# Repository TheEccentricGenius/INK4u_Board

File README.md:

# INK4u_Board

An UNO form factor board with a AVR128DA28 processor.

This board is designed to be the next generation AVR succesor to the UNO R3 using the AVR128DA28 from Microchip.

The board has a number of features, such as a UPDI programming and UART programming onboard.
The on-board UPDI programming means a bootloader can be burned onto the MCU while it is on the board....No more external programmer required for programming via the ISP header!

## Pinout for your INK 4u board.

## How to select a upload mode on your INK 4u board.
<i>Credits for the upload mode design goes to MCUdude.</i>

Locate the upload mode header using the pinout as a guide.
Below the upload mode header will be the words "UART AUTO UPDI", when shipped the AUTO mode is selected.

To select UART mode, move the jumper shunt to above the UART word.
</br>

To select UPDI mode, move the jumper shunt to above the UPDI word.
</br>

Return the jumper shunt to AUTO mode if you desire the board to automatically select UART or UPDI.
</br>

## Using the INK 4u board as a UPDI programmer.
1. Select UPDI mode on the upload mode header using the upload mode jumper.
2. Remove the jumper from the UPDI header.
3. Connect the UPDI chip you desire to program or debug via UPDI, to the UPDI pin on the INK 4u board.
   <br><i>Refer to the UPDI mode picture for the UPDI output pin.</i></br>
5. Wire your chip to the respective Power pin from the INK 4u board and the GND pins.
   <br><i>Refer to the pinout for power and GND pins.</i></br>
7. Connect the INK 4u board to your device via the USB B port.
8. Select the INK 4u COM port as your programmer and program using UPDI as normal.

## Configuring your INK 4u board to run in 3.3V mode.
1. Disconnect your board from any power source.
2. Cut the 5V trace as indicated in the photo below.
   </br>

<br><i>Before soldering across the two pads in the blue box, measure the IOREF pin voltage.</i></br>
4. If the IOREF voltage is less then 5V then, solder across the two pads outlined by the blue box.
5. Reconnect the board to a power source, the IOREF voltage should measure close to 3.3V.
   <br><i>If the IOREF voltage is 5V or considerably less then 3.3V repeat the above steps.</i></br>
6. To return the board back to 5V solder across to the pad with the arrow underneath it, and remove the solder connecting to the 3.3V pad.

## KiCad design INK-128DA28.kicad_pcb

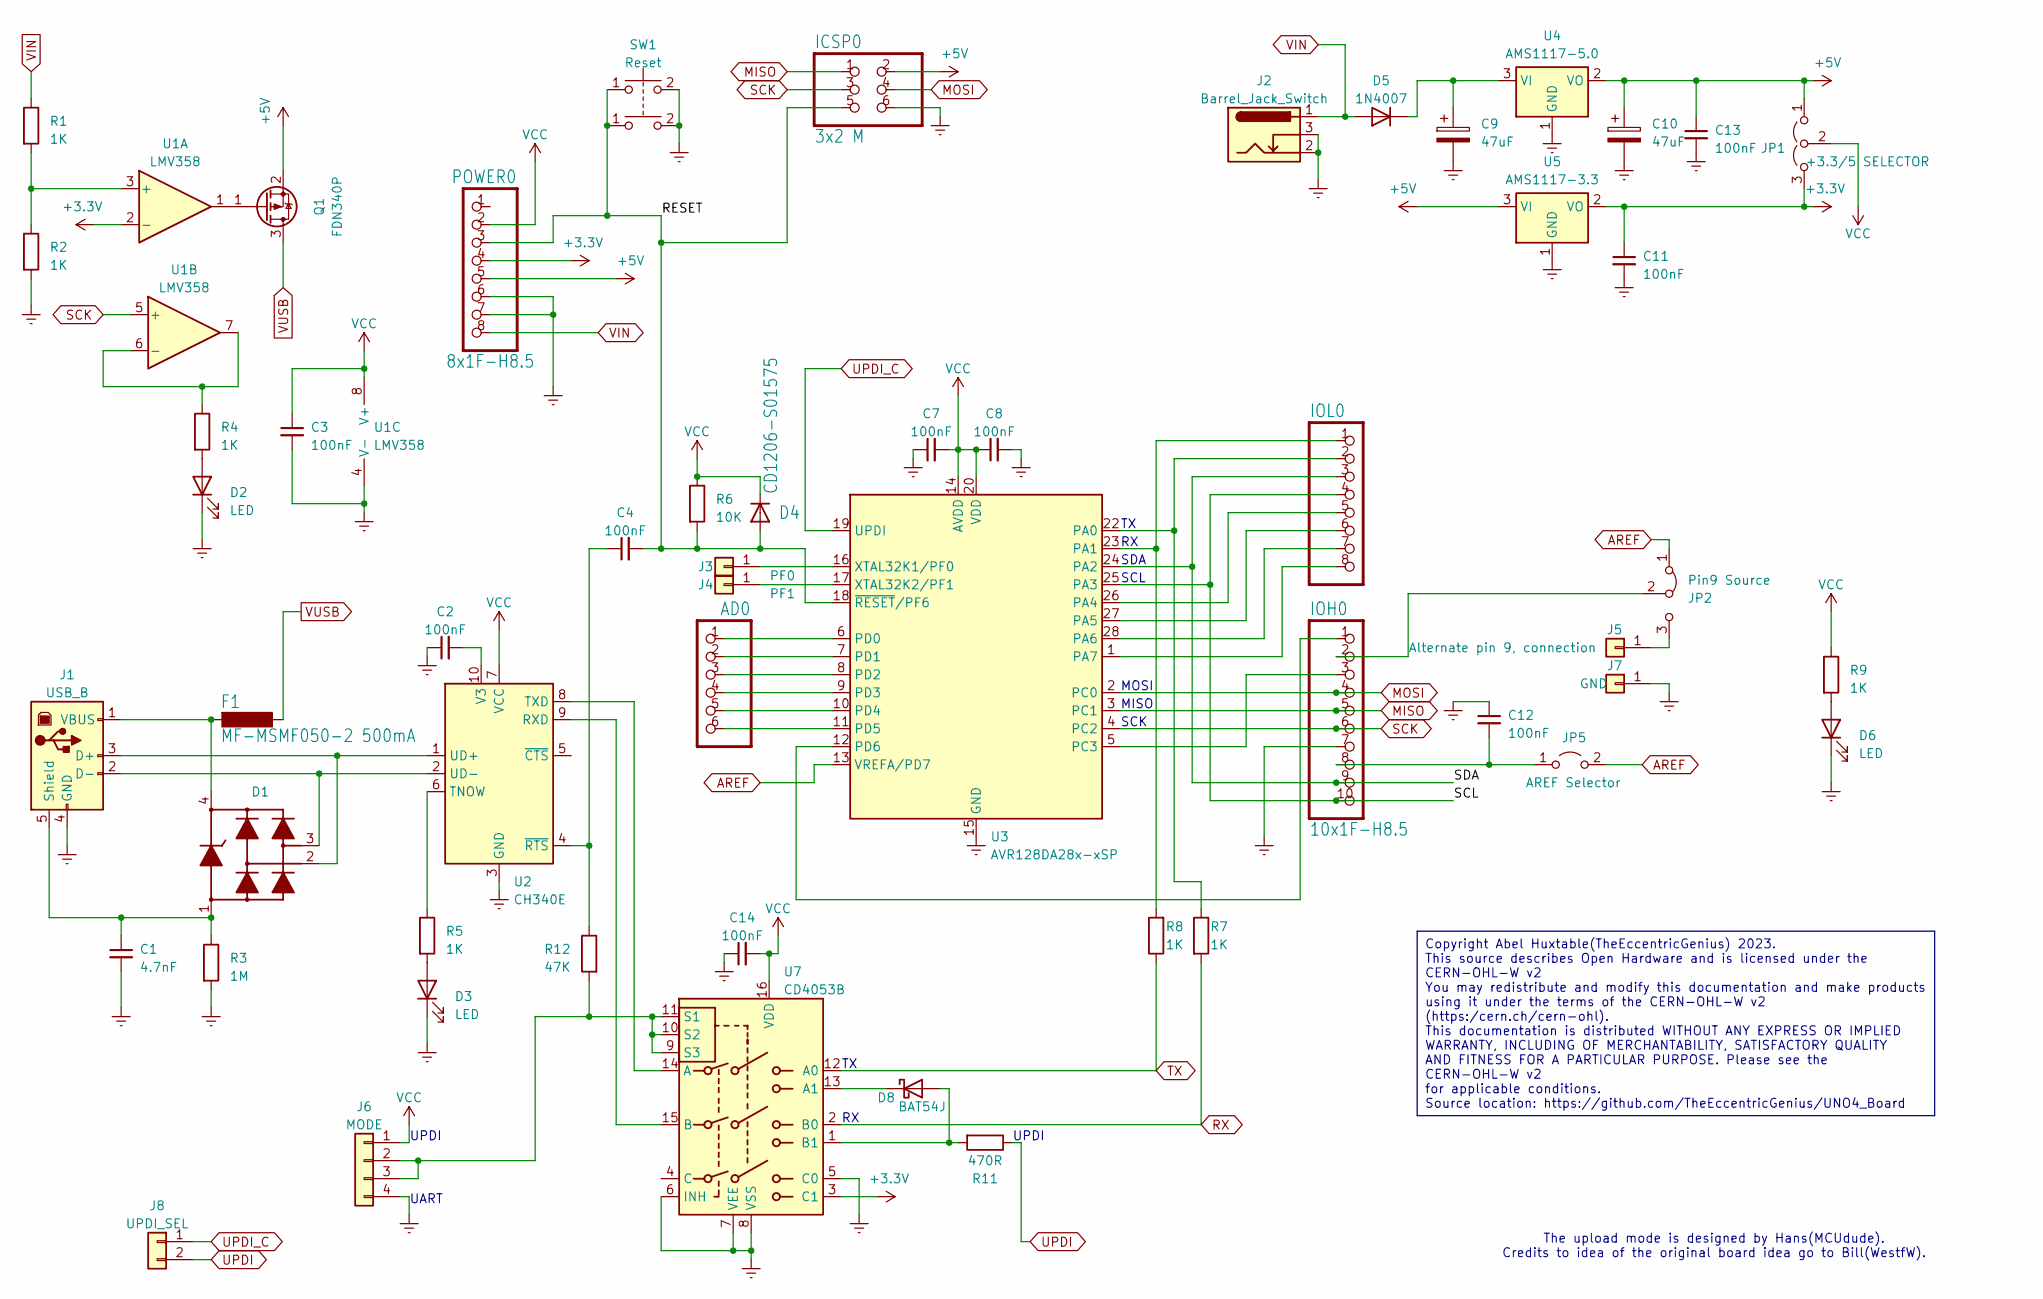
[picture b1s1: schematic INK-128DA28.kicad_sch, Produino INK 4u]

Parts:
AD0: 6x1F-H8.5; PinSocket_1x06_P2.54mm_Vertical
C1: 4.7nF; C_0805_2012Metric_Pad1.18x1.45mm_HandSolder
C2, C3, C4, C7, C8, C11, C12, C13, C14: 100nF; C_0603_1608Metric_Pad1.08x0.95mm_HandSolder
C9, C10: 47uF; CP_Radial_D5.0mm_P2.50mm
D1: PRTR5V0U2X,215; SOT-143_Handsoldering; PART NUMBER PRTR5V0U2X,215
D2, D3, D6: LED; LED_0805_2012Metric_Pad1.15x1.40mm_HandSolder
D4: CD1206-S01575; MINIMELF
D5: 1N4007; D_DO-41_SOD81_P10.16mm_Horizontal
D8: BAT54J; D_SOD-323F
F1: MF-MSMF050-2 500mA; Fuse_1812_4532Metric_Pad1.30x3.40mm_HandSolder
ICSP0: 3x2 M; PinHeader_2x03_P2.54mm_Vertical
IOH0: 10x1F-H8.5; PinSocket_1x10_P2.54mm_Vertical
IOL0: 8x1F-H8.5; PinSocket_1x08_P2.54mm_Vertical
J1: USB_B
J2: Barrel_Jack_Switch; BarrelJack
J3: PF0; SolderWirePad_1x01_SMD_1x2mm
J4: PF1; SolderWirePad_1x01_SMD_1x2mm
J5: Alternate pin 9, connection; SolderWirePad_1x01_SMD_1x2mm
J6: MODE; PinHeader_1x04_P2.54mm_Vertical
J7: GND; SolderWirePad_1x01_SMD_1x2mm
J8: UPDI_SEL; PinHeader_1x02_P2.54mm_Vertical
JP1: +3.3/5 SELECTOR; SolderJumper-3_P1.3mm_Bridged12_RoundedPad1.0x1.5mm
JP2: Pin9 Source; SolderJumper-3_P1.3mm_Bridged12_RoundedPad1.0x1.5mm
JP5: AREF Selector; SolderJumper-2_P1.3mm_Open_RoundedPad1.0x1.5mm
POWER0: 8x1F-H8.5; PinSocket_1x08_P2.54mm_Vertical
Q1: FDN340P; SOT-23
R1, R2, R4, R5, R7, R8, R9: 1K; R_0603_1608Metric_Pad0.98x0.95mm_HandSolder
R3: 1M; R_0603_1608Metric_Pad0.98x0.95mm_HandSolder
R6: 10K; R_0603_1608Metric_Pad0.98x0.95mm_HandSolder
R11: 470R; R_0603_1608Metric_Pad0.98x0.95mm_HandSolder
R12: 47K; R_0603_1608Metric_Pad0.98x0.95mm_HandSolder
SW1: Reset; SW_PUSH_6mm
U1: LMV358; SO-8_3.9x4.9mm_P1.27mm
U2: CH340E; MSOP-10_3x3mm_P0.5mm
U3: AVR128DA28x-xSP; DIP-28_W7.62mm
U4: AMS1117-5.0; SOT-223-3_TabPin2
U5: AMS1117-3.3; SOT-223-3_TabPin2
U7: CD4053B; TSSOP-16_4.4x5mm_P0.65mm

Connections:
+3.3V: C11.1, JP1.3 (B), POWER0.4, U1.2 (-), U5.2 (VO), U7.3 (C1)
+5V: C10.1, C13.1, ICSP0.2, JP1.1 (A), POWER0.5, Q1.2 (S), U4.2 (VO), U5.3 (VI)
/RESET: C4.2, D4.A, ICSP0.5, POWER0.3, R6.2, SW1.1 (3), U3.18 (~RESET/PF6)
/SCL: IOH0.10, IOL0.4, U3.25 (PA3)
/SDA: IOH0.9, IOL0.3, U3.24 (PA2)
AREF: JP2.1 (A), JP5.2 (B), U3.13 (VREFA/PD7)
Earth: C1.2, C2.1, C3.2, C7.1, C8.2, C9.2, C10.2, C11.2, C12.1, C13.2, C14.1, D2.1 (K), D3.1 (K), D6.1 (K), ICSP0.6, IOH0.7, J1.4 (GND), J2.2, J2.3, J6.4, J7.1, POWER0.6, POWER0.7, R2.2, R3.2, SW1.2 (4), U1.4 (V-), U2.3 (GND), U3.15 (GND), U3.21 (GND), U4.1 (GND), U5.1 (GND), U7.5 (C0), U7.6 (INH), U7.7 (VEE), U7.8 (VSS)
MISO: ICSP0.1, IOH0.5, U3.3 (PC1)
MOSI: ICSP0.4, IOH0.4, U3.2 (PC0)
unnamed: D2.2 (A), R4.2
unnamed: D3.2 (A), R5.2
unnamed: C9.1, D5.1 (K), U4.3 (VI)
unnamed: D6.2 (A), R9.2
unnamed: D8.2 (A), R11.2, U7.1 (B1)
unnamed: D8.1 (K), U7.13 (A1)
unnamed: D1.2, J1.3 (D+), U2.1 (UD+)
unnamed: D1.3, J1.2 (D-), U2.2 (UD-)
unnamed: C1.1, D1.1, J1.5 (Shield), R3.1
unnamed: D1.4, F1.2, J1.1 (VBUS)
unnamed: J3.1, U3.16 (XTAL32K1/PF0)
unnamed: J4.1, U3.17 (XTAL32K2/PF1)
unnamed: J5.1, JP2.3 (B)
unnamed: J6.2, J6.3, R12.2, U7.9 (S3), U7.10 (S2), U7.11 (S1)
unnamed: IOH0.2, JP2.2 (C)
unnamed: C12.2, IOH0.8, JP5.1 (A)
unnamed: Q1.1 (G), U1.1
unnamed: R1.2, R2.1, U1.3 (+)
unnamed: R4.1, U1.6 (-), U1.7
unnamed: U2.9 (RXD), U7.15 (B)
unnamed: R5.1, U2.6 (TNOW)
unnamed: U2.8 (TXD), U7.14 (A)
unnamed: C2.2, U2.10 (V3)
unnamed: C4.1, R12.1, U2.4 (~RTS)
unnamed: IOL0.2, R7.1, U3.22 (PA0)
unnamed: IOL0.1, R8.2, U3.23 (PA1)
unnamed: IOL0.5, U3.26 (PA4)
unnamed: IOL0.6, U3.27 (PA5)
unnamed: IOL0.7, U3.28 (PA6)
unnamed: IOL0.8, U3.1 (PA7)
unnamed: IOH0.3, U3.5 (PC3)
unnamed: AD0.1, U3.6 (PD0)
unnamed: AD0.2, U3.7 (PD1)
unnamed: AD0.3, U3.8 (PD2)
unnamed: AD0.4, U3.9 (PD3)
unnamed: AD0.5, U3.10 (PD4)
unnamed: AD0.6, U3.11 (PD5)
unnamed: IOH0.1, U3.12 (PD6)
RX: R7.2, U7.2 (B0)
SCK: ICSP0.3, IOH0.6, U1.5 (+), U3.4 (PC2)
TX: R8.1, U7.12 (A0)
UPDI: J8.2, R11.1
UPDI_C: J8.1, U3.19 (UPDI)
VCC: C3.1, C7.2, C8.1, C14.2, D4.C, J6.1, JP1.2 (C), POWER0.2, R6.1, R9.1, U1.8 (V+), U2.7 (VCC), U3.14 (AVDD), U3.20 (VDD), U7.16 (VDD)
VIN: D5.2 (A), J2.1, POWER0.8, R1.1
VUSB: F1.1, Q1.3 (D)

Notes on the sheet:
Copyright Abel Huxtable(TheEccentricGenius) 2023. This source describes Open Hardware and is licensed under the CERN-OHL-W v2 You may redistribute and modify this documentation and make products using it under the terms of the CERN-OHL-W v2 (https:/cern.ch/cern-ohl). This documentation is distribut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
UART
SCK
SDA
MISO
SCL
UPDI
MOSI
The upload mode is designed by Hans(MCUdude). Credits to idea of the original board idea go to Bill(WestfW).

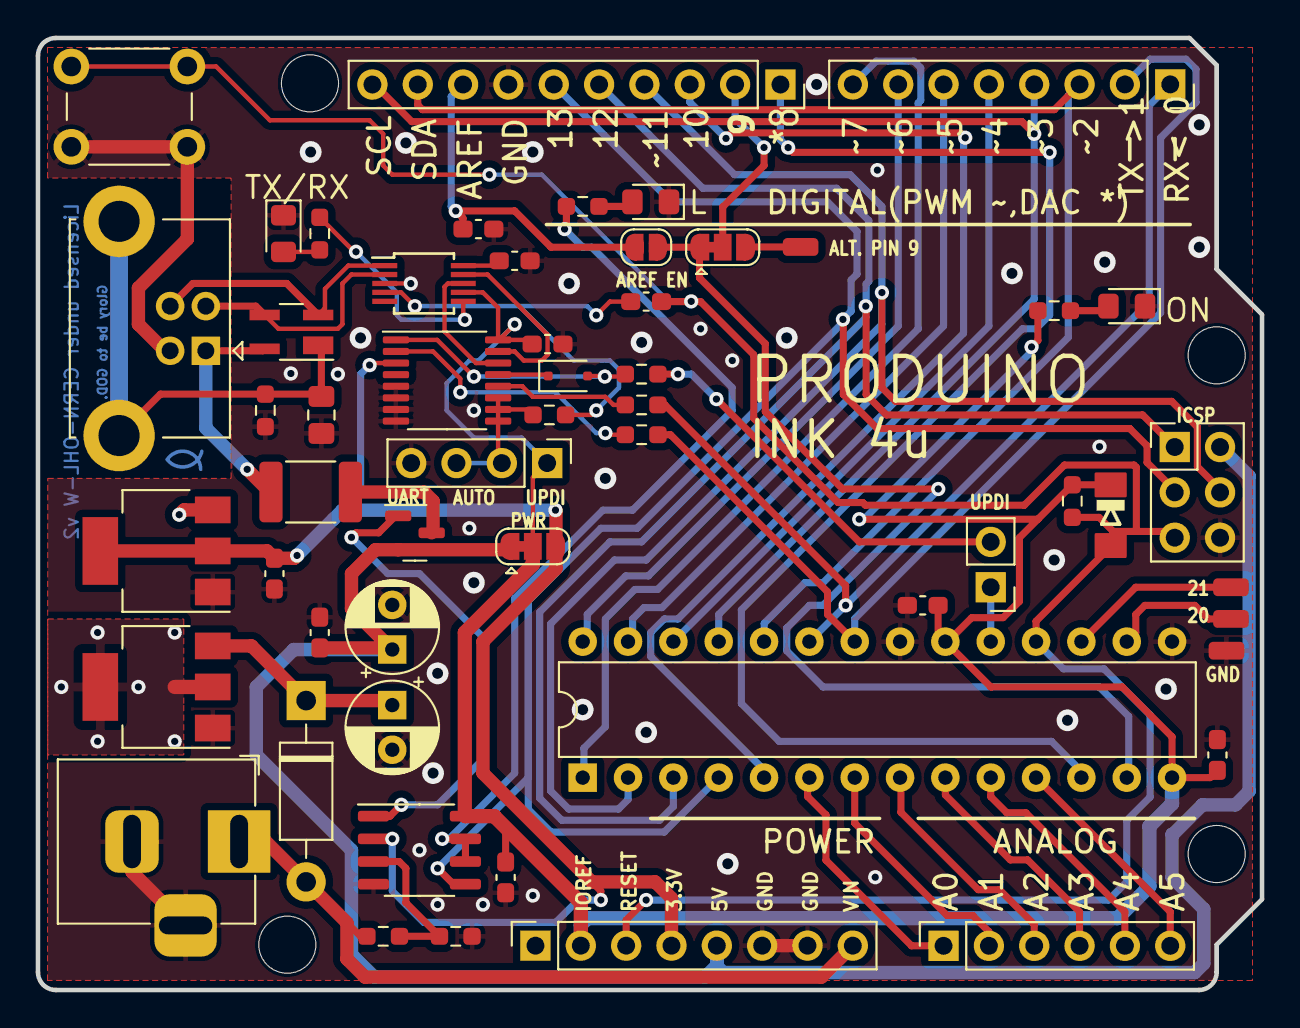
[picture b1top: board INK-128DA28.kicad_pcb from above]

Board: 2 copper layers, 68.6 x 53.3 mm, 59 parts (0 on the bottom side), 55 nets.

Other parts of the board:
@HOLE0, @HOLE1, @HOLE2, @HOLE3: (no value)

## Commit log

2025-11-12 Update README.md
    Renamed UNO to INK due to licensing constraints around the use of UNO.
2025-11-12 Delete UNO-128DA28-GERBERS.zip
    Due to renaming issues.
2025-11-12 Delete UNO-128DA28.kicad_pcb
    Due to renaming issues.
2025-11-12 Delete UNO-128DA28.kicad_prl
    Due to renaming issues.
2025-11-12 Delete UNO-128DA28.kicad_pro
    Due to renaming issues.
2025-11-12 Delete UNO-128DA28.kicad_sch
    Due to renaming issues.
2025-11-12 Updates to the board due to licensing issues.
2025-11-12 Delete gbr directory
    Due to renaming issues.
2025-11-12 Fixes to prevent license issues with "UNO".

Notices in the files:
INK-128DA28.kicad_pcb:
Licensed under CERN-OHL-W v2
